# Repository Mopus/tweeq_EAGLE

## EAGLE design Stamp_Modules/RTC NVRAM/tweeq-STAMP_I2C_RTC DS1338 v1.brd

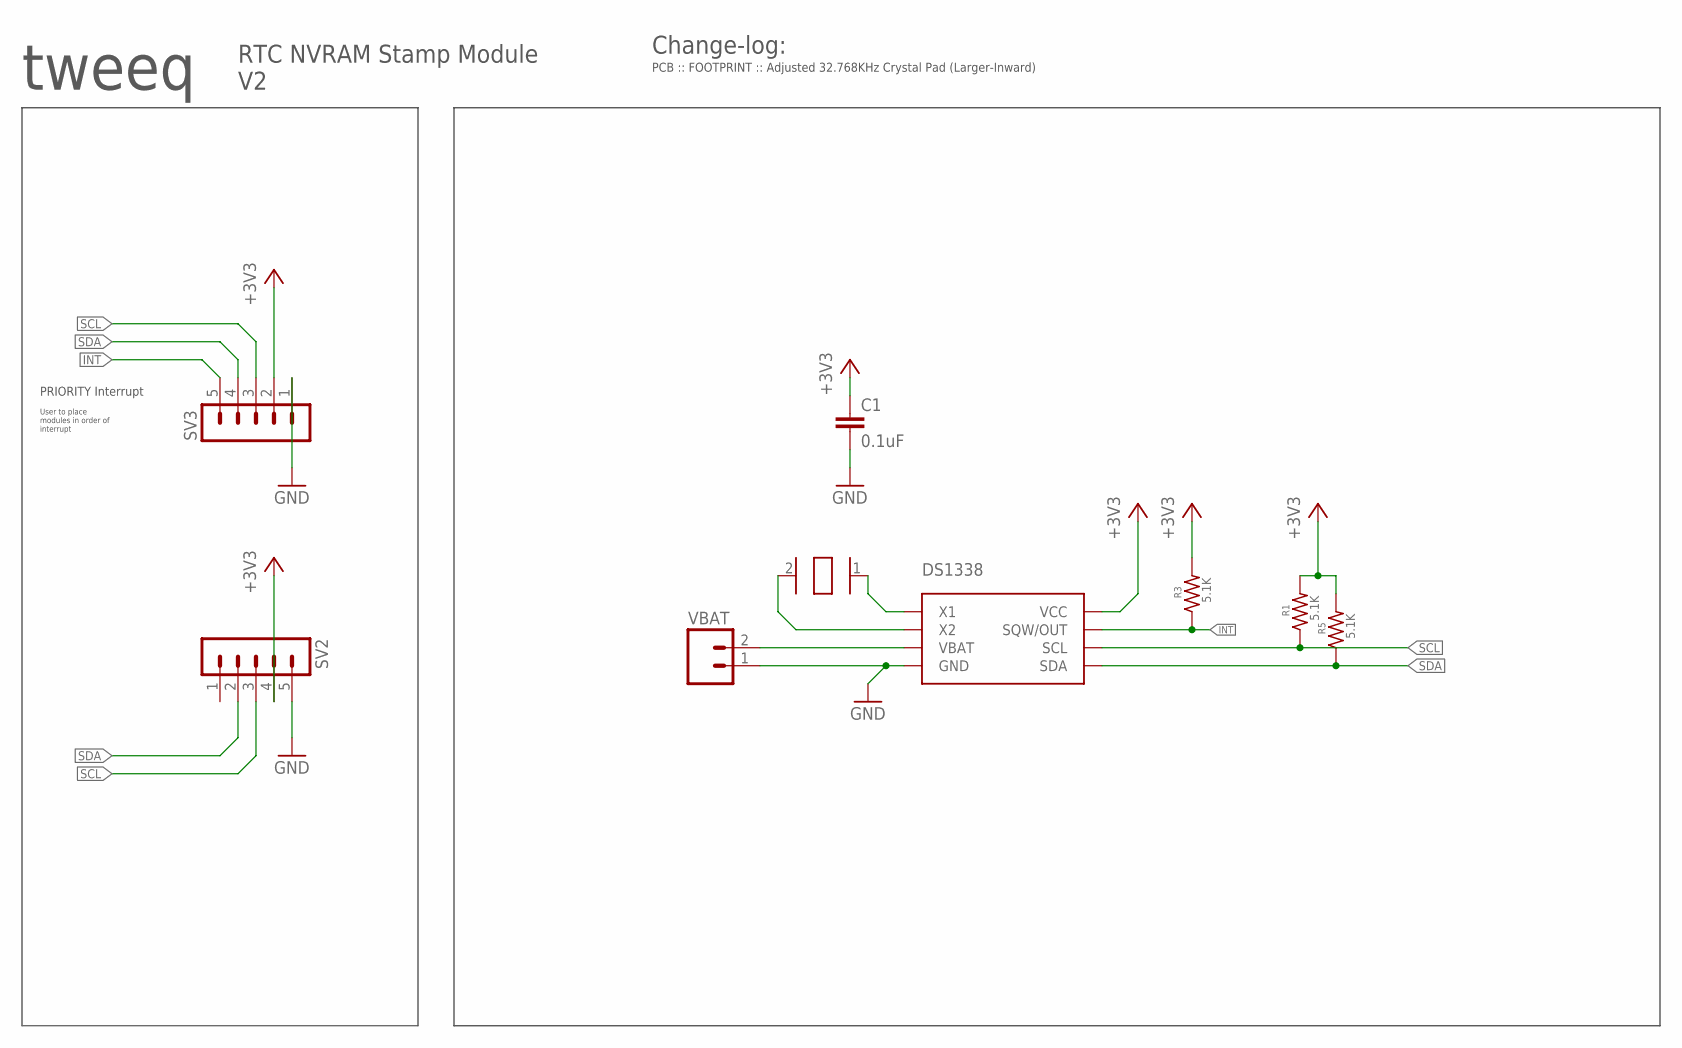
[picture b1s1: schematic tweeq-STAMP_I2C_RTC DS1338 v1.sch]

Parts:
C1: 0.1uF; C0402K
DS1338: DS1338U; MSOP8
R1, R3, R5: 5.1K; R0402
SV2, SV3: M05-1STAMP; 1X05-1.5MM-STAMP
U$2: 32.765KHZ_CRYSTALABS07; ABS07
VBAT: M021X02_SMD_SQUARE; 1X02_SMD

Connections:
+3V3: C1.1, DS1338.8 (VCC), R1.2, R3.2, R5.2, SV2.4, SV3.2
GND: C1.2, DS1338.4 (GND), SV2.5, SV3.1, VBAT.1
INT: DS1338.7 (SQW/OUT), R3.1, SV3.5
unnamed: DS1338.2 (X2), U$2.2
unnamed: DS1338.1 (X1), U$2.1
unnamed: DS1338.3 (VBAT), VBAT.2
SCL: DS1338.6 (SCL), R1.1, SV2.3, SV3.3
SDA: DS1338.5 (SDA), R5.1, SV2.2, SV3.4

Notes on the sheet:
tweeq
RTC NVRAM Stamp Module V2
PRIORITY Interrupt
User to place modules in order of interrupt
Change-log:
PCB :: FOOTPRINT :: Adjusted 32.768KHz Crystal Pad (Larger-Inward)

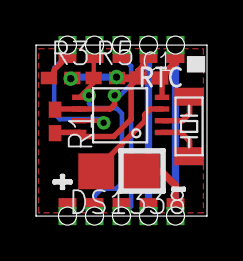
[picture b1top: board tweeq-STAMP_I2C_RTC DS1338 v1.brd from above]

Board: 2 copper layers, 9.5 x 9.5 mm, 10 parts (1 on the bottom side), 8 nets.

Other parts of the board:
U$1: TWEEQ-LOGO-S

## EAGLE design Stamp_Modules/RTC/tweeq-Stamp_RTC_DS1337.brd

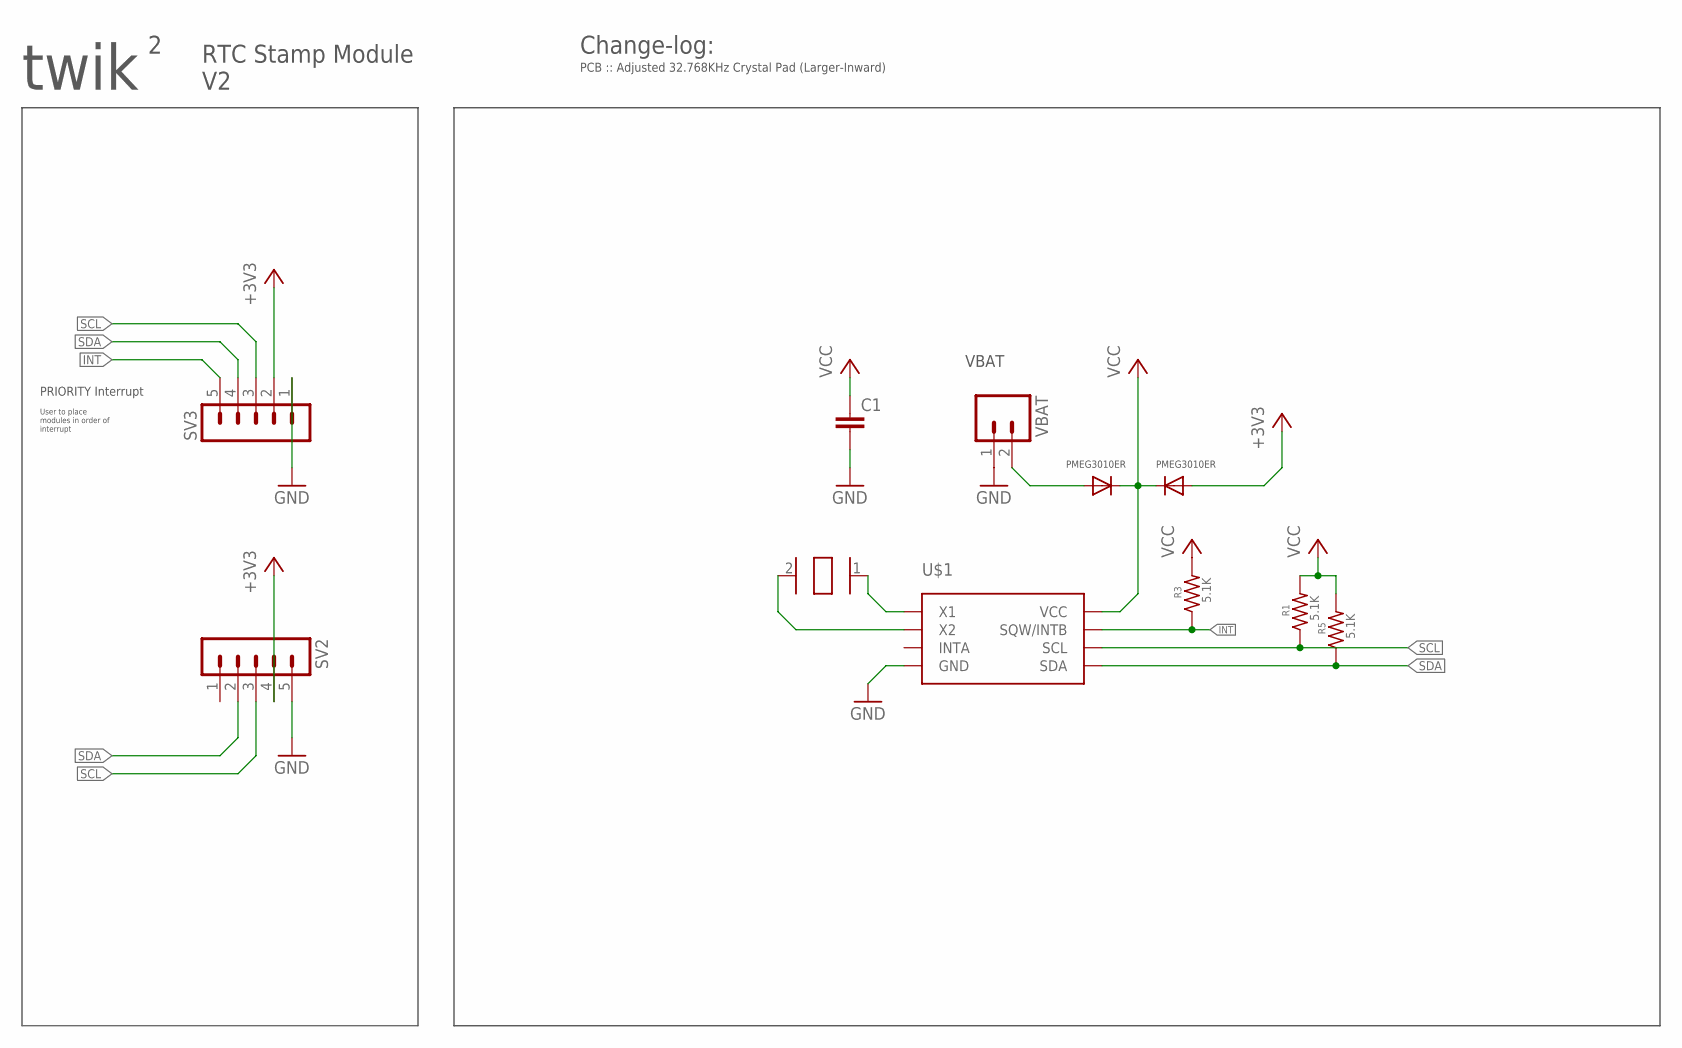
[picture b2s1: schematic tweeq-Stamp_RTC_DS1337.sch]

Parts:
C1: C-EUC0402K; C0402K
R1, R3, R5: 5.1K; R0402
SV2, SV3: M05-1STAMP; 1X05-1.5MM-STAMP
U$1: DS1337SO; MSOP8
U$2: 32.765KHZ_CRYSTALABS07; ABS07
U$4, U$6: PMEG3010ER/MOD; SOD123-MOD
VBAT: M021X02_SMD_SQUARE; 1X02_SMD

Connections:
+3V3: SV2.4, SV3.2, U$6.A
GND: C1.2, SV2.5, SV3.1, U$1.4 (GND), VBAT.1
INT: R3.1, SV3.5, U$1.7 (SQW/INTB)
unnamed: U$1.2 (X2), U$2.2
unnamed: U$1.1 (X1), U$2.1
SCL: R1.1, SV2.3, SV3.3, U$1.6 (SCL)
SDA: R5.1, SV2.2, SV3.4, U$1.5 (SDA)
VBAT: U$4.A, VBAT.2
VCC: C1.1, R1.2, R3.2, R5.2, U$1.8 (VCC), U$4.C, U$6.C

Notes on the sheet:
PMEG3010ER
VBAT
twik
RTC Stamp Module V2
PRIORITY Interrupt
User to place modules in order of interrupt
Change-log:
PCB :: Adjusted 32.768KHz Crystal Pad (Larger-Inward)

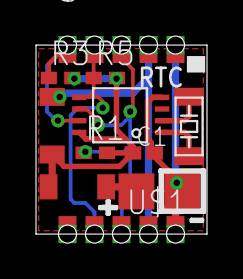
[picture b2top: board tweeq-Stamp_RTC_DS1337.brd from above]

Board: 2 copper layers, 9.5 x 10.5 mm, 12 parts (1 on the bottom side), 9 nets.

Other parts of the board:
U$3: TWEEQ-LOGO-S

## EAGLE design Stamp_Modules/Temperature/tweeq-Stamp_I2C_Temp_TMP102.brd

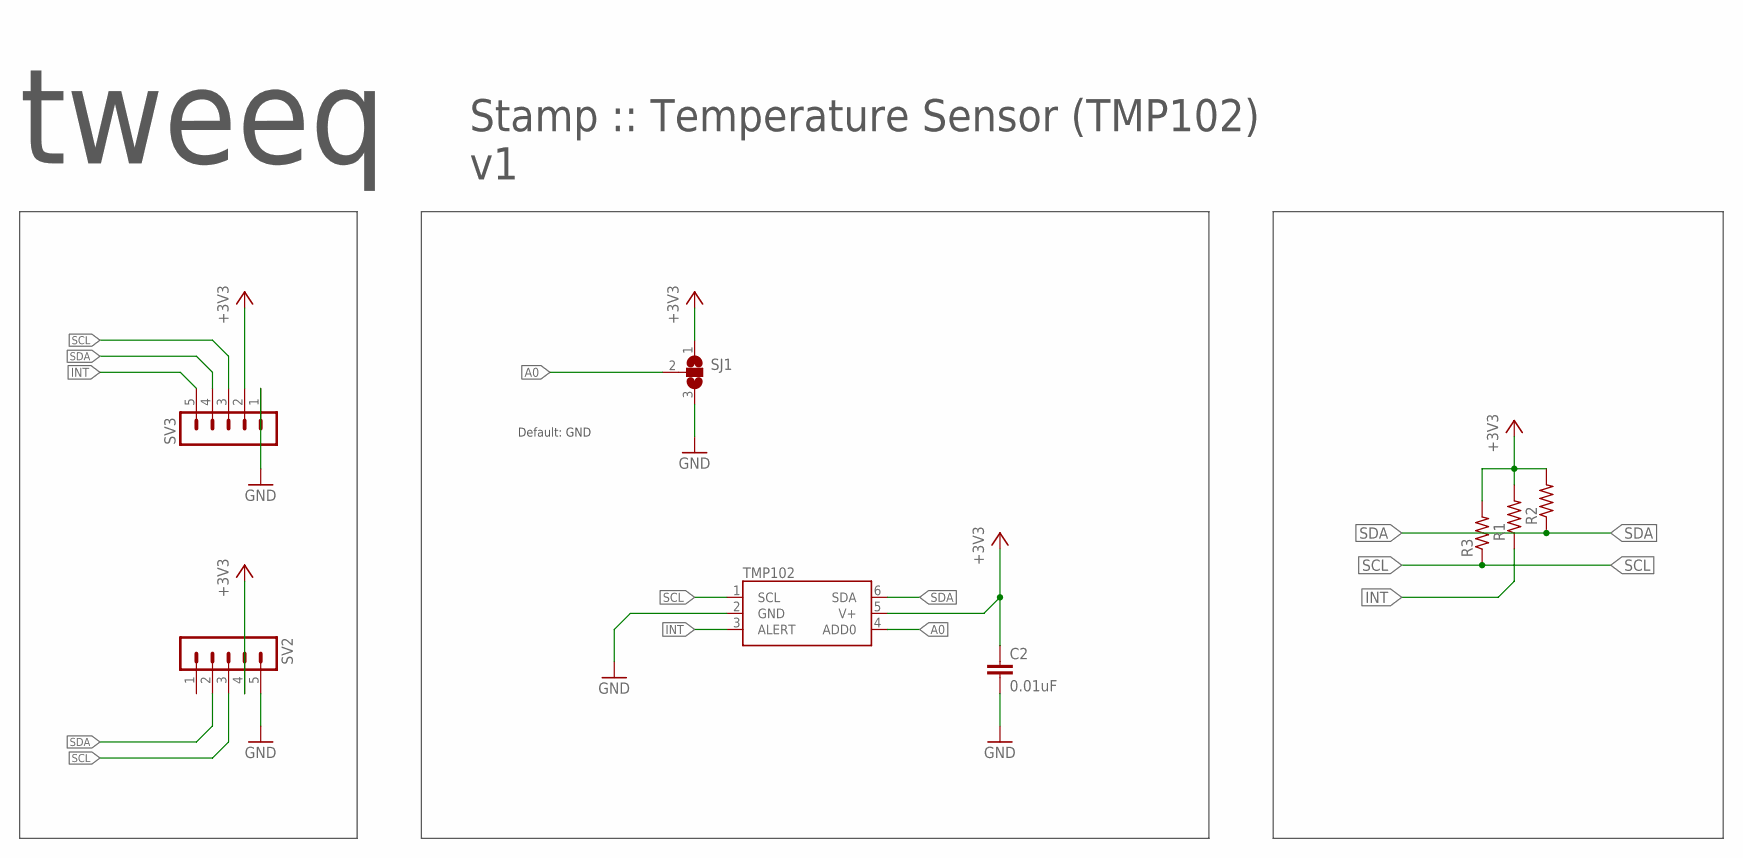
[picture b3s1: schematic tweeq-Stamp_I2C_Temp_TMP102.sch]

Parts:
C2: 0.01uF; C0402K
R1, R2, R3: R-US_R0402; R0402
SJ1: JUMPER_SJ2WS; JUMPER_SJ_S
SV2, SV3: M05-1STAMP; 1X05-1.5MM-STAMP
TMP102: TMP102/SOT563; SOT563

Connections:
+3V3: C2.1, R1.2, R2.2, R3.2, SJ1.1, SV2.4, SV3.2, TMP102.5 (V+)
A0: SJ1.2, TMP102.4 (ADD0)
GND: C2.2, SJ1.3, SV2.5, SV3.1, TMP102.2 (GND)
INT: R1.1, SV3.5, TMP102.3 (ALERT)
SCL: R3.1, SV2.3, SV3.3, TMP102.1 (SCL)
SDA: R2.1, SV2.2, SV3.4, TMP102.6 (SDA)

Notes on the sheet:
Default: GND
tweeq
Stamp :: Temperature Sensor (TMP102) v1

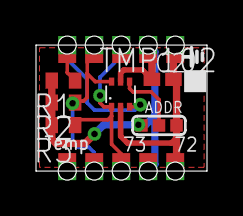
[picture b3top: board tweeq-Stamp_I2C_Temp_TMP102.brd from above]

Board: 2 copper layers, 9.5 x 7.0 mm, 9 parts (1 on the bottom side), 6 nets.

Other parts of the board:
U$1: TWEEQ-LOGO-S
